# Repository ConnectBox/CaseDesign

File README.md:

# CaseDesign
Repo to store the STL/STEP and Fusion 360 files for the project

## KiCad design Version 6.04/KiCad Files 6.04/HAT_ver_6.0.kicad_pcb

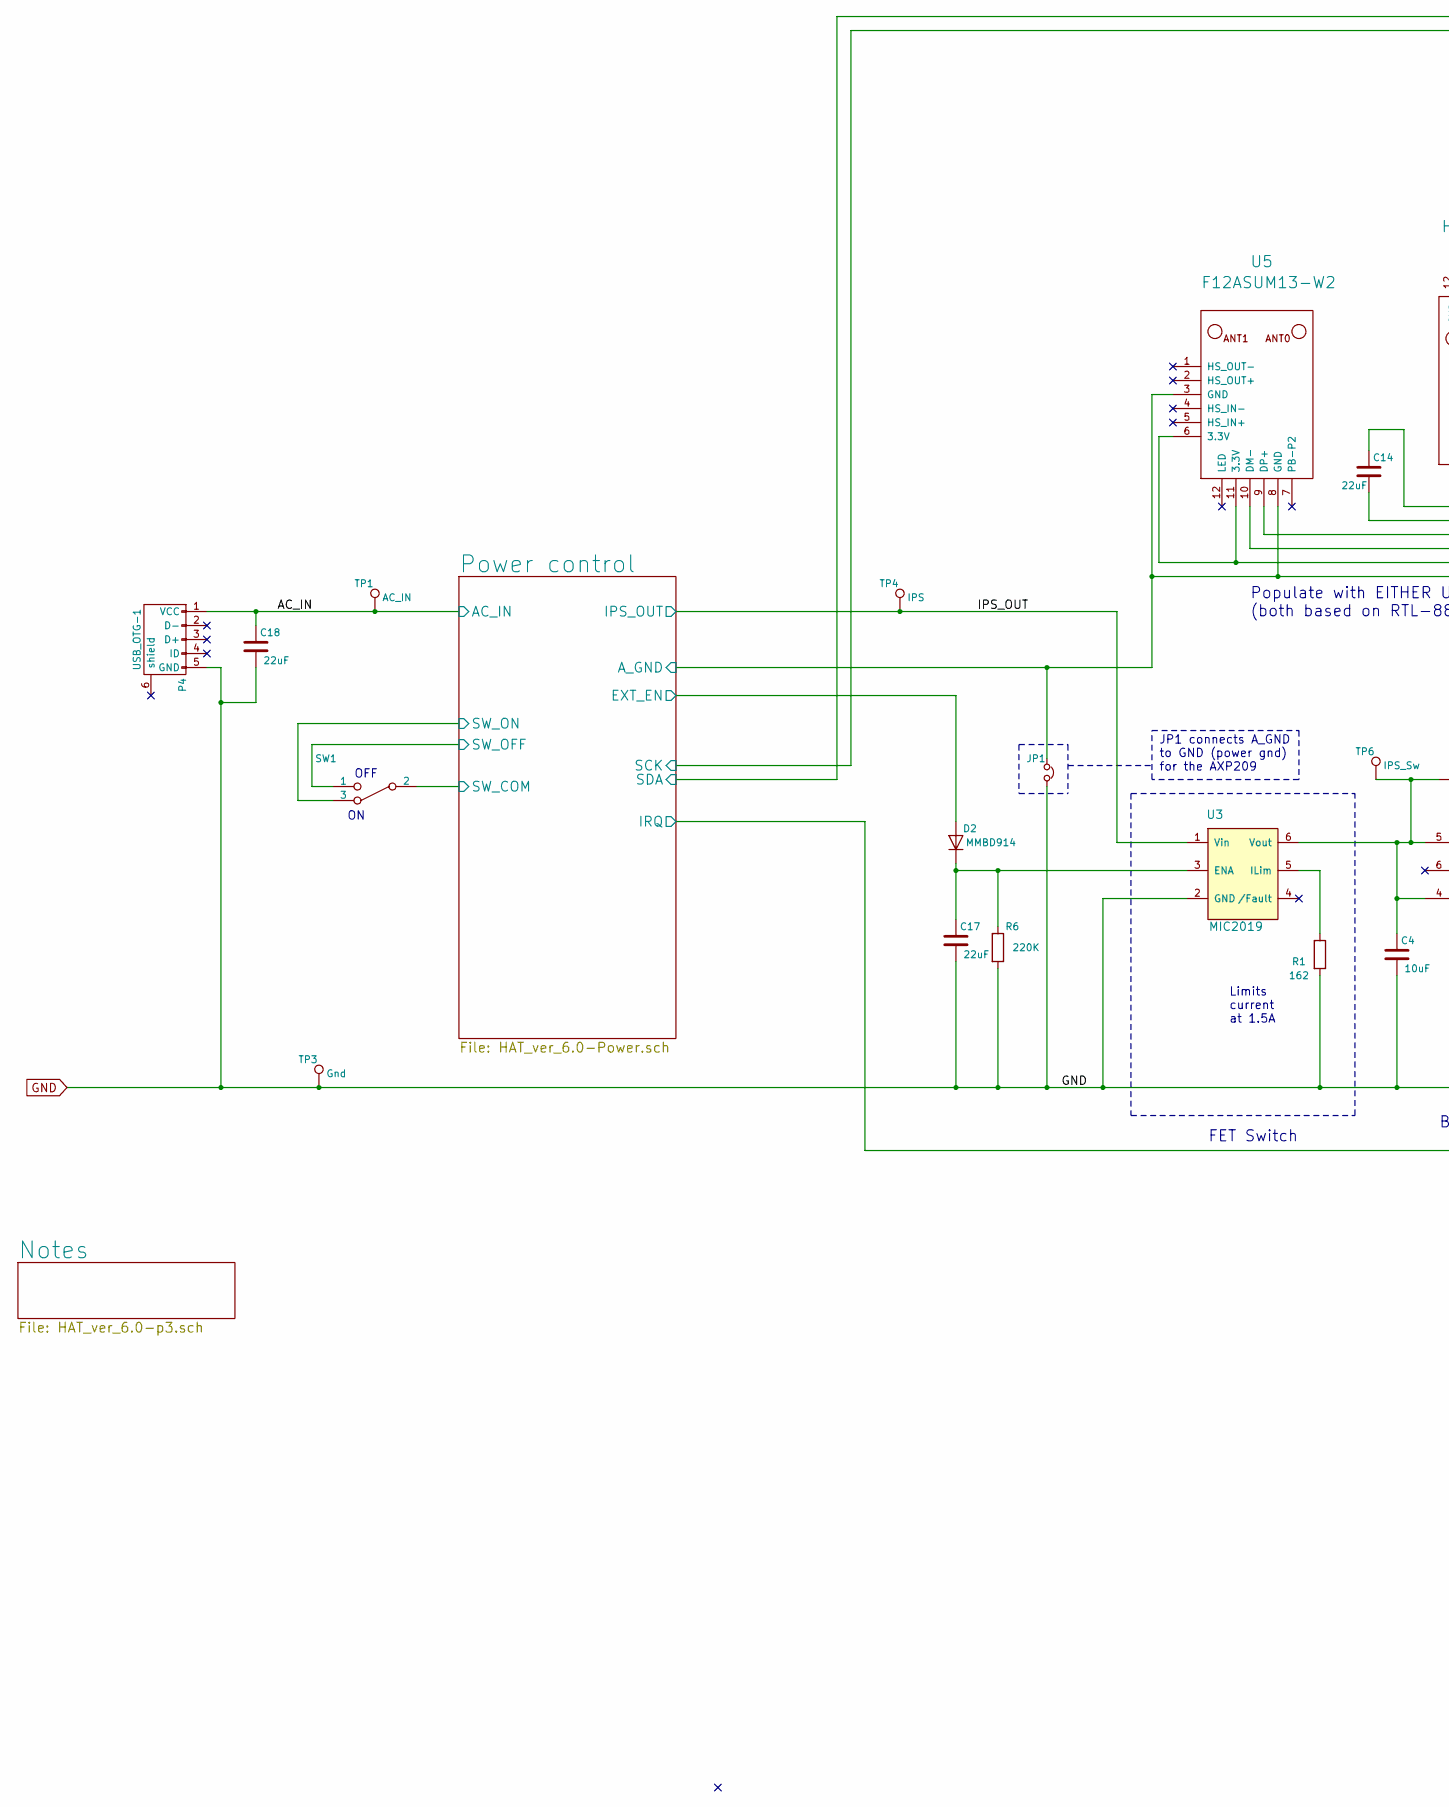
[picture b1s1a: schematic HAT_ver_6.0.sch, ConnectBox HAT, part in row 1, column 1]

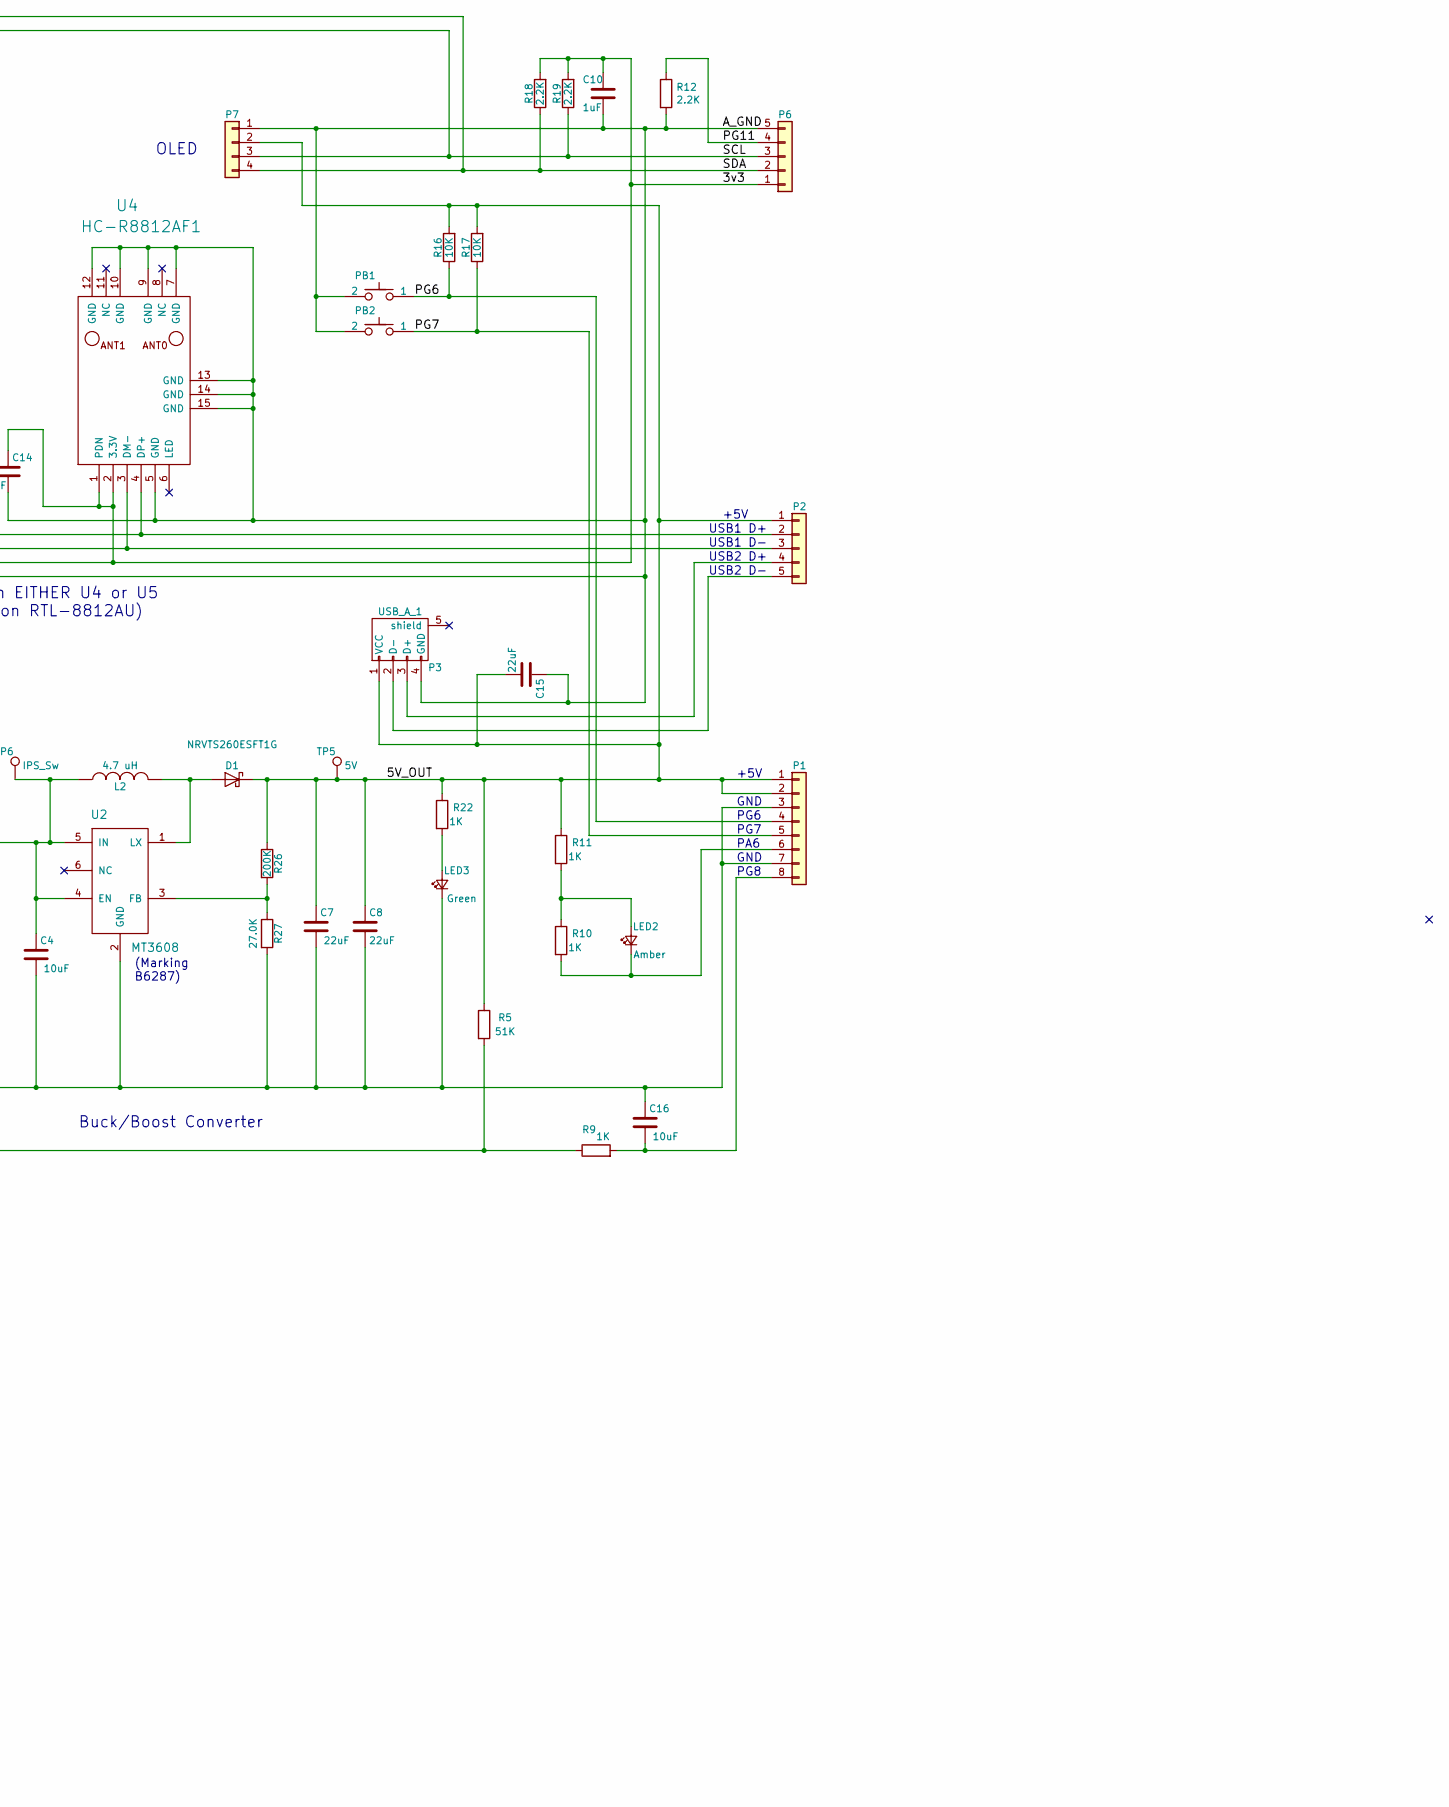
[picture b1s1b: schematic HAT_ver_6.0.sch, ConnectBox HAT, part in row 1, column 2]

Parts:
C4, C16: 10uF; C_0805_2012Metric; Manufacturer P/N CL21A106MPFNNNE; DigiKey P/N 1276-1144-1-ND
C7, C8, C14, C15, C17, C18: 22uF; C_0805_2012Metric; Manufacturer P/N C0805C226M8PAC7800; DigiKey P/N 399-12069-1-ND
C10: 1uF; C_0805_2012Metric; Manufacturer P/N C0805C105K8PACTU; DigiKey P/N 399-8006-1-ND
D1: NRVTS260ESFT1G; SOD-123FL; Manufacturer P/N NRVTS260ESFT1G; DigiKey P/N NRVTS260ESFT1GOSCT-ND
D2: MMBD914; D_SOT-23_ANK; Manufacturer P/N MMBD914LT1G; DigiKey P/N MMBD914LT1GOSCT-ND
JP1: Jumper_NC_Small; NetConnect
L2: 4.7 uH; INDUCTOR_SMD_6x6-1; Manufacturer P/N NR6028T4R7M; DigiKey P/N 587-2100-1-ND
LED2: Amber; LED_0603_1608Metric; Manufacturer P/N LTST-C191KFKT; DigiKey P/N 160-1445-1-ND
LED3: Green; LED_0603_1608Metric; Manufacturer P/N LTST-C191KFKT; DigiKey P/N 160-1446-1-ND
P1: Conn_01x08; PinHeader_1x08_P2.54mm_Vertical; Manufacturer P/N PPPC081LFBN-RC; DigiKey P/N S7041-ND
P2, P6: Conn_01x05; PinHeader_1x05_P2.54mm_Vertical; Manufacturer P/N PPPC051LFBN-RC; DigiKey P/N S7038-ND
P3: USB_A_1; USB_A; Manufacturer P/N USB-A1HSW6; DigiKey P/N ED2989-ND
P4: USB_OTG-1; USB_Micro-B-TH-mount; Manufacturer P/N 10118194-0001LF; DigiKey P/N 609-4618-1-ND
P7: Conn_01x04; PinHeader_1x04_P2.54mm_Vertical; Manufacturer P/N PPPC041LFBN-RC; DigiKey P/N S7037-ND
PB1, PB2: SPST-PUSH; SW-TL3305; Manufacturer P/N TL3305AF260QG; DigiKey P/N EG5353CT-ND
R1: 162; R_0805_2012Metric; Manufacturer P/N RC0805FR-07162R; DigiKey P/N 311-162CRCT-ND
R5: 51K; R_0805_2012Metric; Manufacturer P/N RC0805FR-071KL; DigiKey P/N 311-51.0KCRCT-ND
R6: 220K; R_0805_2012Metric; Manufacturer P/N RC0805FR-07220KL; DigiKey P/N 311-220KCRCT-ND
R9, R10, R11, R22: 1K; R_0805_2012Metric; Manufacturer P/N RC0805FR-071KL; DigiKey P/N 311-1.00KCRCT-ND
R12, R18, R19: 2.2K; R_0805_2012Metric; Manufacturer P/N RC0805FR-072K2L; DigiKey P/N 311-2.20KCRCT-ND
R16, R17: 10K; R_0805_2012Metric; Manufacturer P/N RC0805FR-0710KL; DigiKey P/N 311-10.0KCRCT-ND
R26: 200K; R_0805_2012Metric; Manufacturer P/N RC0805FR-07200KL; DigiKey P/N 311-200KCRCT-ND
R27: 27.0K; R_0805_2012Metric; Manufacturer P/N RC0805FR-0727KL; DigiKey P/N 311-27.0KCRCT-ND
SW1: SPDT-2C; SPDT-OS10211; Manufacturer P/N OS102011MA1QN1; DigiKey P/N CKN9559-ND or CKN9560-ND
TP1: AC_IN; TestPoint_THTPad_D1.5mm_Drill0.7mm
TP3: Gnd; TestPoint_THTPad_D1.5mm_Drill0.7mm
TP4: IPS; TestPoint_THTPad_D1.5mm_Drill0.7mm
TP5: 5V; TestPoint_THTPad_D1.5mm_Drill0.7mm
TP6: IPS_Sw; TestPoint_THTPad_D1.5mm_Drill0.7mm
U2: MT3608; SOT-23-6a; Manufacturer P/N MT3608
U3: MIC2019; SOT-23-6a; Manufacturer P/N MIC2019YM6-TR; DigiKey P/N 576-2595-1-ND
U4: HC-R8812AF1; HC-R8812AU2-th-1
U5: F12ASUM13-W2

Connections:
/3v3: C10.1, C14.1, P6.1, R18.2, R19.2, U4.1 (PDN), U4.2 (3.3V), U5.6 (3.3V), U5.11 (3.3V)
/5V_OUT: C7.1, C8.1, C15.2, D1.1 (K), P1.1, P1.2, P2.1, P3.1 (VCC), P7.2, R5.1, R11.1, R16.2, R17.2, R22.1, R26.1, TP5.1
/AC_IN: C18.1, P4.1 (VCC), TP1.1; also elsewhere on the board
/A_GND: C10.2, C14.2, C15.1, JP1.1, P3.4 (GND), P6.5, P7.1, PB1.2, PB2.2, R12.2, U4.5 (GND), U4.7 (GND), U4.9 (GND), U4.10 (GND), U4.12 (GND), U4.13 (GND), U4.14 (GND), U4.15 (GND), U5.3 (GND), U5.8 (GND); also elsewhere on the board
/IPS_OUT: TP4.1, U3.1 (Vin); also elsewhere on the board
/PG6: P1.4, PB1.1, R16.1
/PG7: P1.5, PB2.1, R17.1
/PG11: P6.4, R12.1
/Power control/EXT_EN: D2.2 (A); also elsewhere on the board
/Power control/IRQ: R5.2, R9.1; also elsewhere on the board
/Power control/SW_COM: SW1.2; also elsewhere on the board
/Power control/SW_OFF: SW1.1; also elsewhere on the board
/Power control/SW_ON: SW1.3; also elsewhere on the board
/SCL: P6.3, P7.3, R19.1; also elsewhere on the board
/SDA: P6.2, P7.4, R18.1; also elsewhere on the board
GND: C4.2, C7.2, C8.2, C16.1, C17.2, C18.2, JP1.2, LED3.1 (K), P1.3, P1.7, P4.5 (GND), R1.2, R6.2, R27.2, TP3.1, U2.2 (GND), U3.2 (GND); also elsewhere on the board
unnamed: C4.1, L2.1, TP6.1, U2.4 (EN), U2.5 (IN), U3.6 (Vout)
unnamed: C16.2, P1.8, R9.2
unnamed: C17.1, D2.1 (K), R6.1, U3.3 (ENA)
unnamed: D1.2 (A), L2.2, U2.1 (LX)
unnamed: LED2.1 (K), P1.6, R10.2
unnamed: LED2.2 (A), R10.1, R11.2
unnamed: LED3.2 (A), R22.2
unnamed: P2.2, U4.4 (DP+), U5.9 (DP+)
unnamed: P2.3, U4.3 (DM-), U5.10 (DM-)
unnamed: P2.4, P3.3 (D+)
unnamed: P2.5, P3.2 (D-)
unnamed: R1.1, U3.5 (ILim)
unnamed: R26.2, R27.1, U2.3 (FB)

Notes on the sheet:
+5V
USB1 D+
USB1 D-
Buck/Boost Converter
PG6
Limits current at 1.5A
(Marking B6287)
FET Switch
PG7
PA6
USB2 D+
USB2 D-
Populate with EITHER U4 or U5 (both based on RTL-8812AU)
GND
PG8
OLED
JP1 connects A_GND to GND (power gnd) for the AXP209
OFF

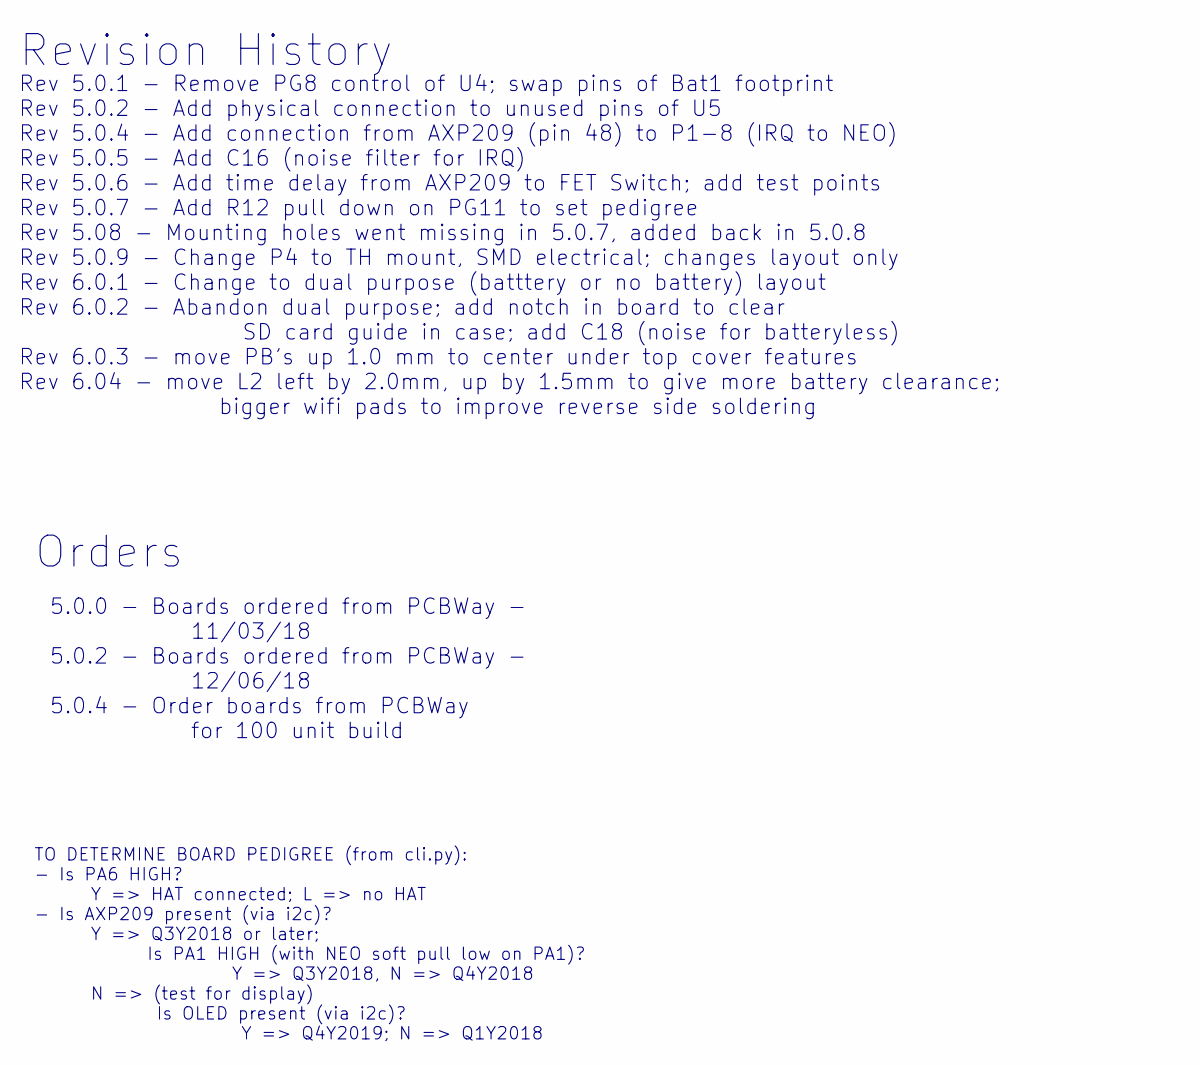
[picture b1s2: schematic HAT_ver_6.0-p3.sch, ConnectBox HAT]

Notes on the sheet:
Rev 5.0.1 - Remove PG8 control of U4; swap pins of Bat1 footprint Rev 5.0.2 - Add physical connection to unused pins of U5 Rev 5.0.4 - Add connection from AXP209 (pin 48) to P1-8 (IRQ to NEO) Rev 5.0.5 - Add C16 (noise filter for IRQ) Rev 5.0.6 - Add time delay from AXP209 to FET Switch; add test p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
Revision History
5.0.0 - Boards ordered from PCBWay - 11/03/18 5.0.2 - Boards ordered from PCBWay - 12/06/18 5.0.4 - Order boards from PCBWay for 100 unit build
Orders
TO DETERMINE BOARD PEDIGREE (from cli.py): - Is PA6 HIGH? Y => HAT connected; L => no HAT - Is AXP209 present (via i2c)? Y => Q3Y2018 or later; Is PA1 HIGH (with NEO soft pull low on PA1)? Y => Q3Y2018, N => Q4Y2018 N => (test for display) Is OLED present (via i2c)? Y => Q4Y2019; N => Q1Y2018

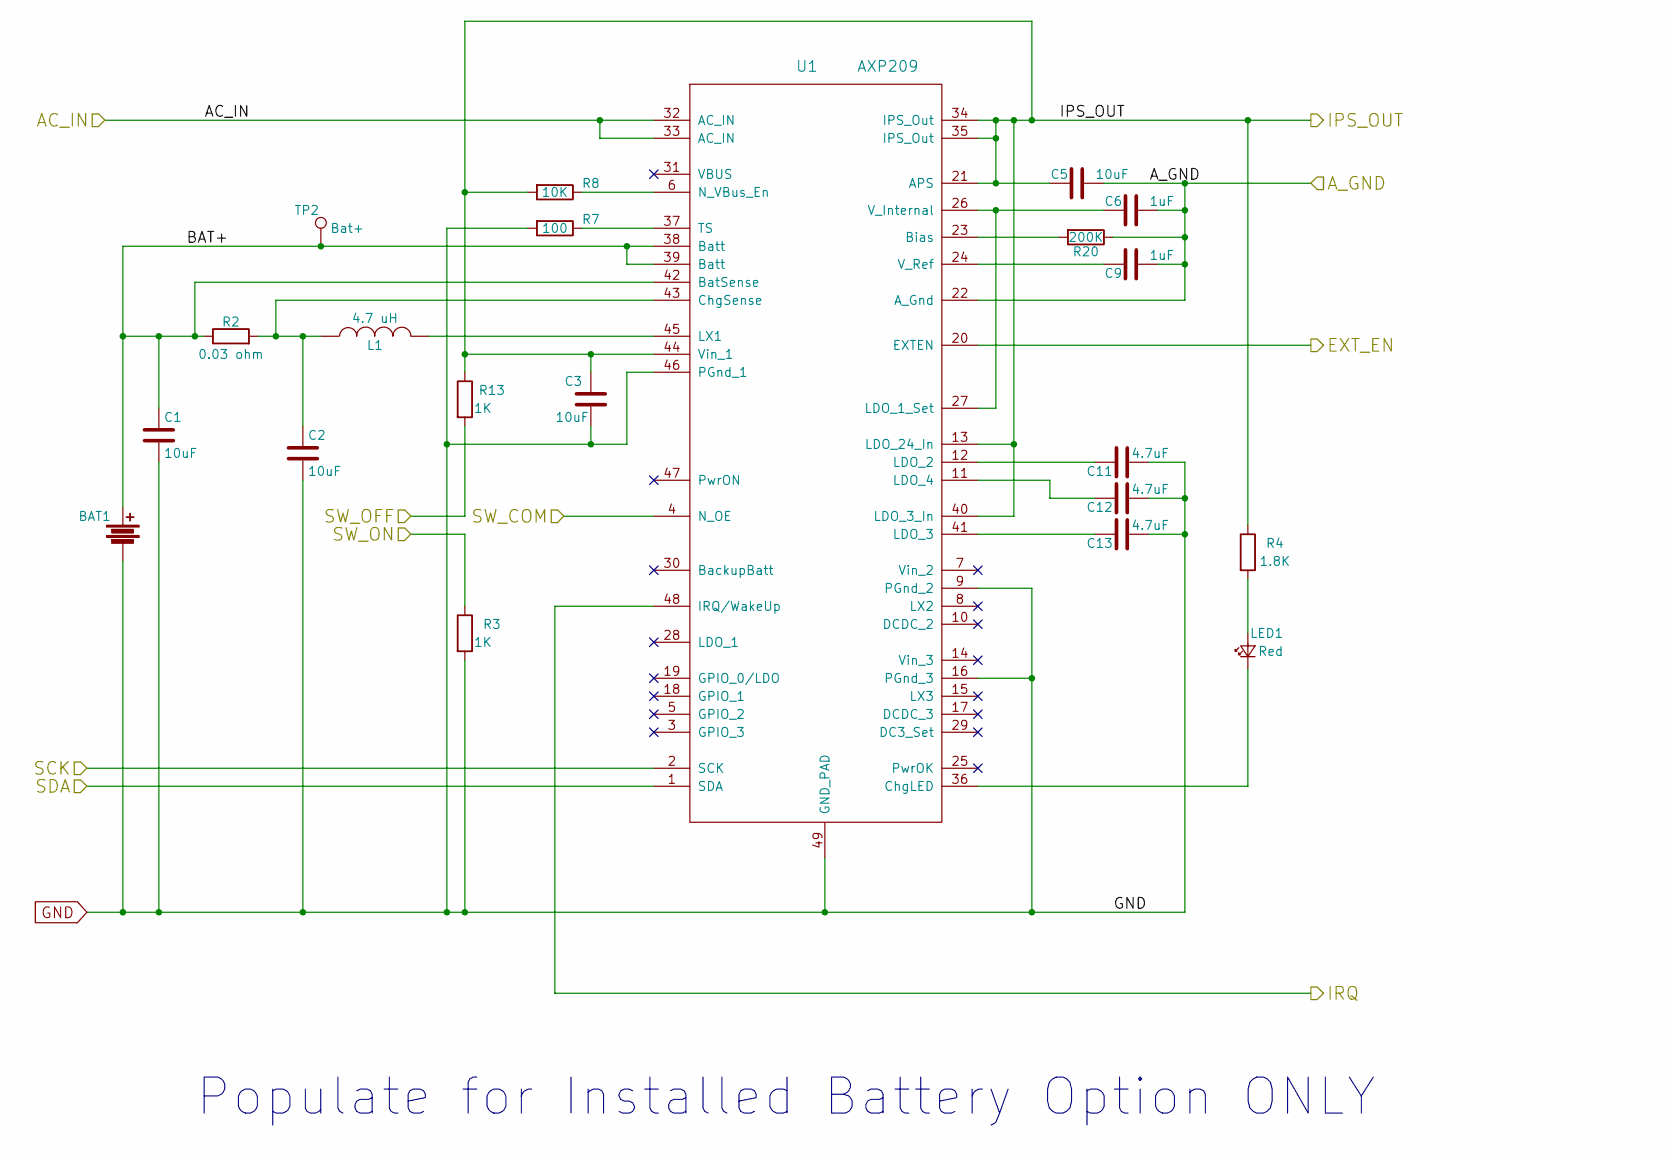
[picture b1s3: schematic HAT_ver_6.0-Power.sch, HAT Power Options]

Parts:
BAT1: Molex PicoBlade 53047-0210; Molex PicoBlade 53047-0210 - (swapped pins); Manufacturer P/N 0530470210; DigiKey P/N WM1731-ND
C1, C2, C3, C5: 10uF; C_0805_2012Metric; Manufacturer P/N CL21A106MPFNNNE; DigiKey P/N 1276-1144-1-ND
C6, C9: 1uF; C_0805_2012Metric; Manufacturer P/N C0805C105K8PACTU; DigiKey P/N 399-8006-1-ND
C11, C12, C13: 4.7uF; C_0805_2012Metric; Manufacturer P/N CL21B475KPFNNNE; DigiKey P/N 1276-2972-1-ND
L1: 4.7 uH; INDUCTOR_SMD_6x6-1; Manufacturer P/N NR6028T4R7M; DigiKey P/N 587-2100-1-ND
LED1: Red; LED_0603_1608Metric; Manufacturer P/N LTST-C191KRKT; DigiKey P/N 160-1447-1-ND
R2: 0.03 ohm; R_0805_2012Metric; Manufacturer P/N ERJ-6CWFR030V; DigiKey P/N P19207CT-ND
R3, R13: 1K; R_0805_2012Metric; Manufacturer P/N RC0805FR-071KL; DigiKey P/N 311-1.00KCRCT-ND
R4: 1.8K; R_0805_2012Metric; Manufacturer P/N RC0805FR-071K8L; DigiKey P/N 311-1.80KCRCT-ND
R7: 100; R_0805_2012Metric; Manufacturer P/N RC0805FR-07100RL; DigiKey P/N 311-100CRCT-ND
R8: 10K; R_0805_2012Metric; Manufacturer P/N RC0805FR-0710KL; DigiKey P/N 311-10.0KCRCT-ND
R20: 200K; R_0805_2012Metric; Manufacturer P/N RC0805FR-07200KL; DigiKey P/N 311-200KCRCT-ND
TP2: Bat+; TestPoint_THTPad_D1.5mm_Drill0.7mm
U1: AXP209; UQFN-48-1EP_6x6mm_Pitch0.4mm_75; Manufacturer P/N AXP209

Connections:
/AC_IN: U1.32 (AC_IN), U1.33 (AC_IN); also elsewhere on the board
/A_GND: C5.1, C6.1, C9.1, R20.1, U1.22 (A_Gnd); also elsewhere on the board
/IPS_OUT: C3.1, C5.2, R4.1, R8.2, R13.1, U1.13 (LDO_24_In), U1.21 (APS), U1.34 (IPS_Out), U1.35 (IPS_Out), U1.40 (LDO_3_In), U1.44 (Vin_1); also elsewhere on the board
/Power control/BAT+: BAT1.1, C1.1, R2.1, TP2.1, U1.38 (Batt), U1.39 (Batt), U1.42 (BatSense)
/Power control/EXT_EN: U1.20 (EXTEN); also elsewhere on the board
/Power control/IRQ: U1.48 (IRQ/WakeUp); also elsewhere on the board
/Power control/SW_COM: U1.4 (N_OE); also elsewhere on the board
/Power control/SW_OFF: R13.2; also elsewhere on the board
/Power control/SW_ON: R3.1; also elsewhere on the board
/SCL: U1.2 (SCK); also elsewhere on the board
/SDA: U1.1 (SDA); also elsewhere on the board
GND: BAT1.2, C1.2, C2.2, C3.2, C11.1, C12.1, C13.1, R3.2, R7.2, U1.9 (PGnd_2), U1.16 (PGnd_3), U1.46 (PGnd_1), U1.49 (GND_PAD); also elsewhere on the board
unnamed: C2.1, L1.1, R2.2, U1.43 (ChgSense)
unnamed: C6.2, U1.26 (V_Internal), U1.27 (LDO_1_Set)
unnamed: C9.2, U1.24 (V_Ref)
unnamed: C11.2, U1.12 (LDO_2)
unnamed: C12.2, U1.11 (LDO_4)
unnamed: C13.2, U1.41 (LDO_3)
unnamed: L1.2, U1.45 (LX1)
unnamed: LED1.1 (K), U1.36 (ChgLED)
unnamed: LED1.2 (A), R4.2
unnamed: R7.1, U1.37 (TS)
unnamed: R8.1, U1.6 (N_VBus_En)
unnamed: R20.2, U1.23 (Bias)

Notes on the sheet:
Populate for Installed Battery Option ONLY

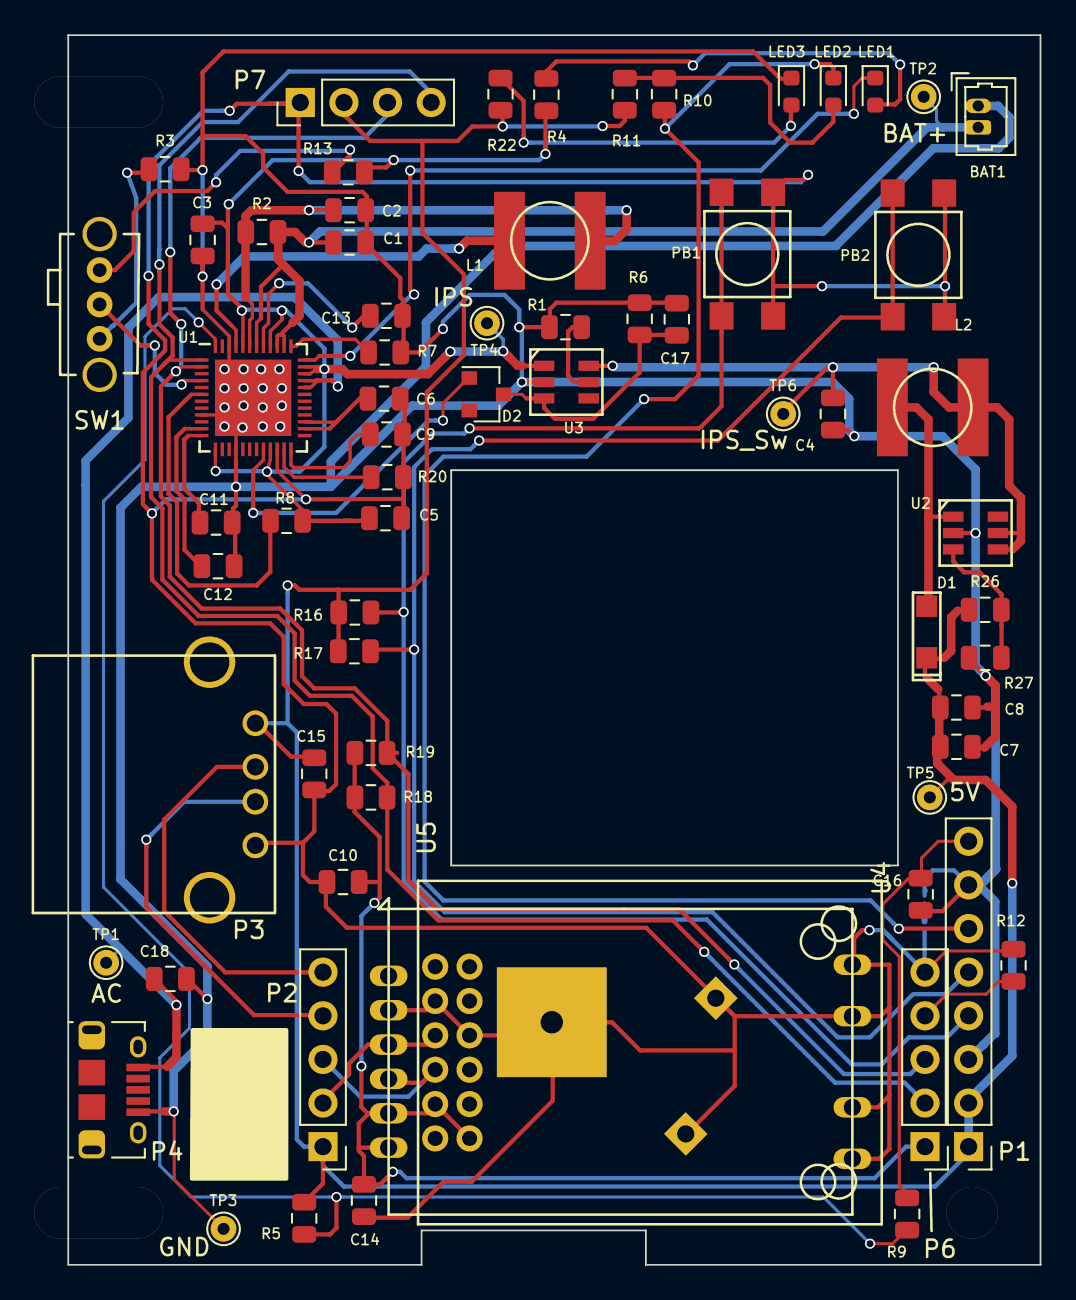
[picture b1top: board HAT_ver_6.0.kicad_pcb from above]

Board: 2 copper layers, 56.6 x 71.6 mm, 68 parts (0 on the bottom side), 42 nets.

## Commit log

2017-11-27 Latest revisions
    These are the final case designs for the 100 unit run
2018-02-07 Version 27 files
    Included the Fusion 360 Files
2018-04-11 Added Version31
2018-07-24 New release version 4.7v8
2018-07-25 Added Gcode and printer setup files
2018-07-25 Added gcode files and printer/slicer initialization
2018-07-25 Corrected version numbers
2019-07-08 Updated for version 5.1 Case Design
2019-11-23 Case Design Changes for Injection Molding
2020-02-10 Updated designs based on molded part design. Both battery version and non battery version.
2021-07-24 new style with USBC and now power switch

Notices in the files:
Version 6.04/KiCad Files 6.04/HAT_ver_6.0.kicad_pcb:
Copyright 2019
